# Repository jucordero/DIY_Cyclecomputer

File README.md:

# DIY Cyclecomputer

Custom made cycle computer / GPS tracker based on the Adafruit Feather Adalogger M0, East Rising ERC240120 240 x 120 pixel monochrome Graphical LCD display, and the Quectel L80-R Serial GPS tracker.

This repository contains everything needed to create a GPS tracker:
- CAD files for the enclosure
- Schematics for the electronics including bill of materials
- Firmware to flash the microcontroller

Electronics were designed using Kicad. __Electronics__ folder contains the KiCAD schematic and board footprint to creathe the main PCB along with the required components to populate it. I'm also including all the libraries used for the not standard parts (GPS, 23-pin screen FPC cable socket, Feather M0, etc.).  
The case was designed using Fusion 360. __Case__ includes the .STEP files for the case, which can be 3D printed in 5 different pieces with minimal support material required. From the .STEP files it should be easy to modify the dimensions to fit different modifications of the design.  
Firmware developed using Arduino. __Firmware__ contains the required .ino files to flash the firmware to the microcontroller. It is based on the Feather Adalogger M0 (ATSAMD21G18 ARM Cortex M0 processor) and can be flashed using either the Arduino IDE or the PlatformIO extension to Atom. The power-on circuit is based on the ATTINY85 and it is intended to provide both powering and control functions.

A few renders and finished prototype

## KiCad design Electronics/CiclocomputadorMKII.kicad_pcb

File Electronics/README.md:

# Electronics

The microcontroller board used is the Adafruit Feather Adalogger M0:
https://learn.adafruit.com/adafruit-feather-m0-adalogger/overview

While not the cheapest option, it provides both the form the factor and ease of integration to the project in terms of not having to bootload
a custom microcontroller chip. Also, having the SD card reader on board facilitates things a lot.
Of course there are plans to move to a completely integrated design, with a fully custom board including the SAM21G18 to drive the display and perfipherals.

The GPS module is the Quectel L80-R. a cheaper version of the L80, with excellent reliability and a reazonable price.
I get them from aliexpress.
The next step is to use the lower profile Quectel L70 plus a chip antenna (GPS1003), which can dramatically reduce the footprint of the main board.

Display module is the East Rising 240 x 120 monochrome LCD display
https://www.buydisplay.com/default/serial-spi-240x120-touch-panel-graphic-lcd-cog-display-connector-fpc
It uses a standard SPI interface and a not so standard 23-pin FPC connector with a 0.5 mm pitch.

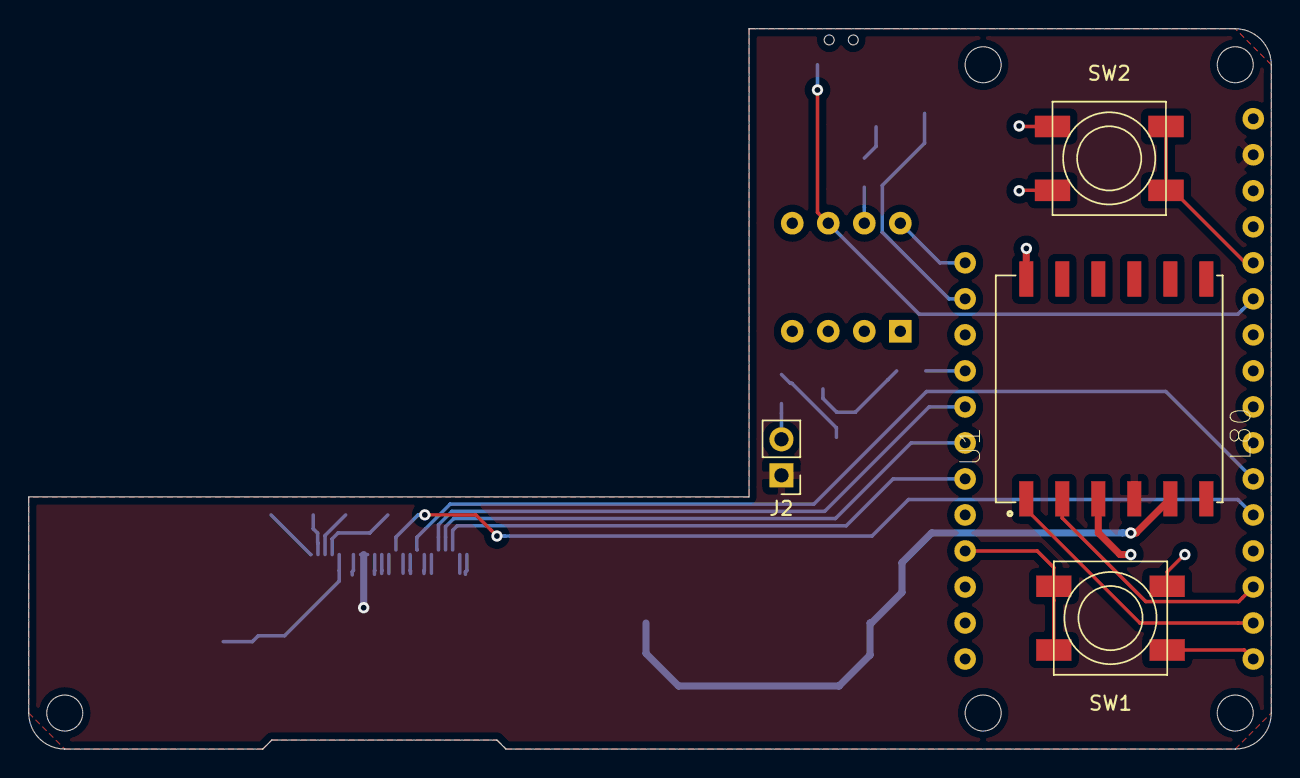
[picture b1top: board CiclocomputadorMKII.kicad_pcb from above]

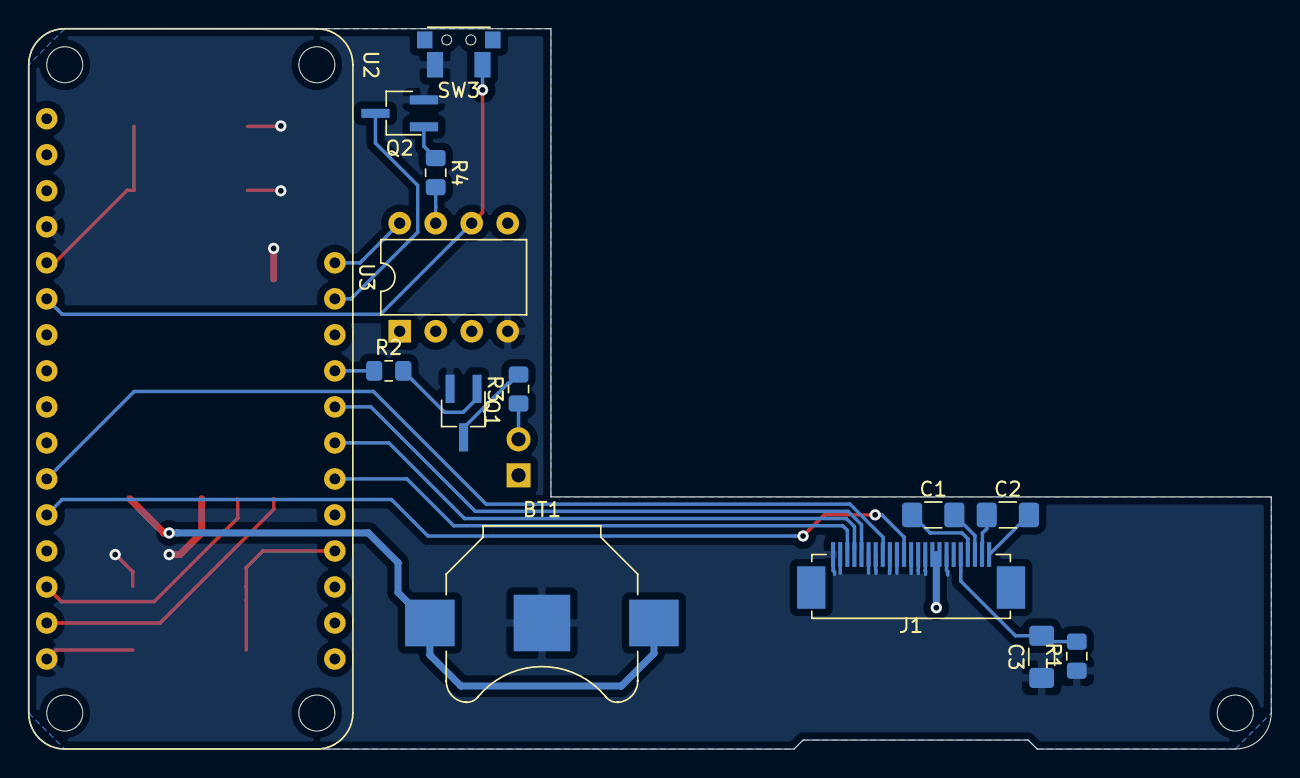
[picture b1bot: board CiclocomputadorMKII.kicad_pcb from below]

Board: 2 copper layers, 87.6 x 50.8 mm, 18 parts (14 on the bottom side), 26 nets.

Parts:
BT1: Battery_Cell; BatteryHolder_Keystone_3000_1x12mm
C1, C2, C3: C; C_1206_3216Metric_Pad1.42x1.75mm_HandSolder
J1: Conn_01x23; FPC_23C_0.5mm
J2: Conn_01x02_Male; PinHeader_1x02_P2.54mm_Vertical
Q1, Q2: Q_NPN_BEC; TSOT-23_HandSoldering
R1, R2, R3, R4: R; R_0805_2012Metric_Pad1.15x1.40mm_HandSolder
SW1, SW2: SW_Push_Dual; SW_DPST_Soft_8mm
SW3: SW_Push; 2x4x3.5mm SMD tactile switch
U1: L80; GPSMODULE_L80
U2: FeatherM0Adalogger; Adafruit_Feather_base
U3: ATtiny85V-10PU; DIP-8_W7.62mm

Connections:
+3V3: J1.15, J1.16, J2.1, U1.4, U2.2
CS: J1.3, U2.22
DC: J1.5, U2.24
EN: Q2.3, U2.27
GND: BT1.2, C3.1, J1.1, J1.2, J1.6, J1.7, J1.9, J1.10, J1.12, J1.13, J1.14, J1.17, Q1.2, Q2.2, R1.1, SW1.2, SW1.4, SW2.2, SW2.4, SW3.1, U1.3, U1.12, U2.4, U2.16, U3.4
LEDPIN: R2.1, U2.25
L_BUTTON: SW1.1, SW1.3, U2.20
MOSI: J1.11, U2.12
unnamed: BT1.1, U1.5
unnamed: C1.1, J1.20
unnamed: C1.2, J1.21
unnamed: C2.1, J1.22
unnamed: C2.2, J1.23
unnamed: C3.2, J1.19, R1.2
unnamed: J2.2, R3.1
unnamed: Q1.1, R2.2
unnamed: Q1.3, R3.2
unnamed: Q2.1, R4.1
unnamed: R4.2, U3.7
unnamed: U1.1, U2.15
unnamed: U1.2, U2.14
RESET: J1.4, U2.23
R_BUTTON: SW2.1, SW2.3, U2.5
SCK: J1.8, U2.11
SIDE_BUTTON: SW3.2, U2.6, U3.6
VBAT: U2.28, U3.8
